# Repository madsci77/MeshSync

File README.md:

# MeshSync
A simple mobile ad hoc network designed to synchronize EL wire or LEDs on Burning Man costumes

I created this project back in 2012 with the goal of building a low cost device (around USD $10) that would plug in between a user's EL wire inverter and the EL wire on their costume or bike and automatically synchronize flashing patterns with other users around them.

It worked pretty well, but it turned out to be nearly impossible to get enough people together at the same time to do any of the more elaborate patterns.  Around 40 units were built.

Also included is a visual simulator written in VB to test out various aspects of the protocol.  It supports automatic partitioning and merging; if a group splits or multiple groups come together, they will automatically reorganize.  Patterns are chosen that are appropriate for the number of group members.

It's a mesh network and in the pathological case of nodes strung out so that each can only hear one node to either side, it'll still converge within a few network cycles.

Very little data is carried over the network; it's just timing information, group membership, and the currently running pattern.

The lowest hardware ID chooses the pattern.  Hardware ID 0 is reserved for a manual control device with a selector button.  Absent a manual control, patterns are chosen randomly.

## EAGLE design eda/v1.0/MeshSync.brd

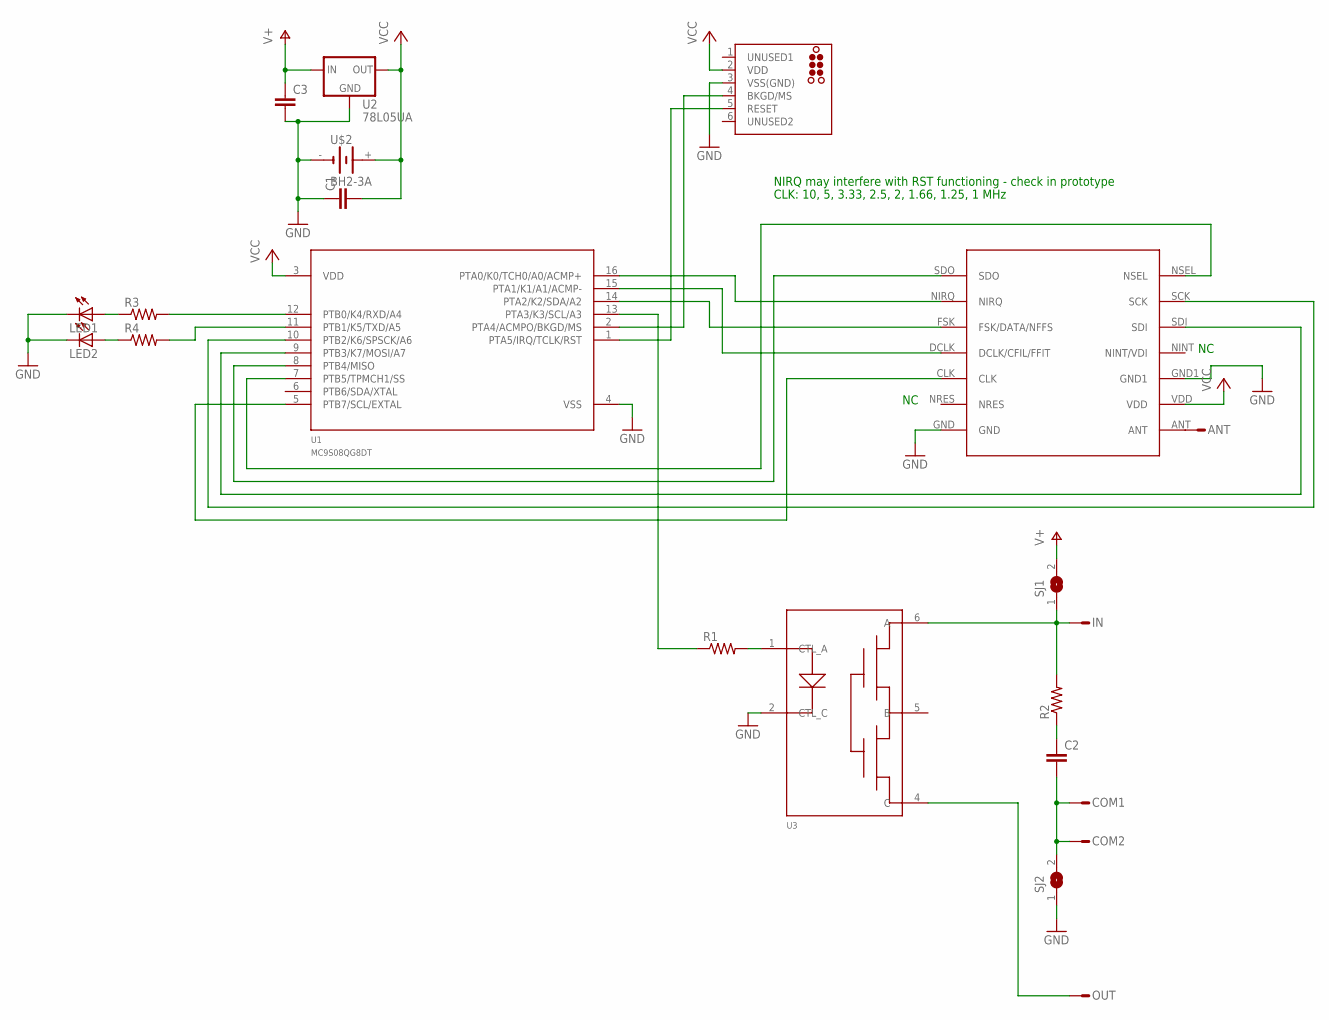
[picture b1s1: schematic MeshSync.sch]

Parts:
ANT: PIN; PINHEAD-1
C1: C-EUC0805K; C0805K
C2, C3: C-EUC0603K; C0603K
COM1, COM2: PIN; PINHEAD-1
IN: PIN; PINHEAD-1
LED1, LED2: LEDCHIPLED_0603; CHIPLED_0603
OUT: PIN; PINHEAD-1
R1, R2, R3, R4: R0603
SJ1, SJ2: SJW
U1: MC9S08QG8DT; TSSOP16
U2: 78L05UA; SOT89
U3: PVT312; DIL06-SMT
U$1: TC2030-MCP-NL
U$2: BH2-3A
XCVR: RFM12B

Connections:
GND: C1.1, C3.2, LED1.C, LED2.C, SJ2.1, U1.4 (VSS), U2.2 (GND), U3.2 (CTL_C), U$1.3 (VSS(GND)), U$2.-, XCVR.GND, XCVR.GND1
unnamed: U1.2 (PTA4/ACMPO/BKGD/MS), U$1.4 (BKGD/MS)
unnamed: U1.1 (PTA5/IRQ/TCLK/RST), U$1.5 (RESET)
unnamed: R1.2, U3.1 (CTL_A)
unnamed: U1.8 (PTB4/MISO), XCVR.SDO
unnamed: U1.9 (PTB3/K7/MOSI/A7), XCVR.SDI
unnamed: U1.10 (PTB2/K6/SPSCK/A6), XCVR.SCK
unnamed: U1.7 (PTB5/TPMCH1/SS), XCVR.NSEL
unnamed: U1.16 (PTA0/K0/TCH0/A0/ACMP+), XCVR.NIRQ
unnamed: U1.5 (PTB7/SCL/EXTAL), XCVR.CLK
unnamed: U1.15 (PTA1/K1/A1/ACMP-), XCVR.DCLK (DCLK/CFIL/FFIT)
unnamed: U1.14 (PTA2/K2/SDA/A2), XCVR.FSK (FSK/DATA/NFFS)
unnamed: ANT.1, XCVR.ANT
unnamed: R1.1, U1.13 (PTA3/K3/SCL/A3)
unnamed: IN.1, R2.2, SJ1.1, U3.6 (A)
unnamed: OUT.1, U3.4 (C)
unnamed: C2.1, R2.1
unnamed: C2.2, COM1.1, COM2.1, SJ2.2
unnamed: R4.2, U1.11 (PTB1/K5/TXD/A5)
unnamed: R3.2, U1.12 (PTB0/K4/RXD/A4)
unnamed: LED1.A, R3.1
unnamed: LED2.A, R4.1
V+: C3.1, SJ1.2, U2.3 (IN)
VCC: C1.2, U1.3 (VDD), U2.1 (OUT), U$1.2 (VDD), U$2.+, XCVR.VDD

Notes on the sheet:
CLK: 10, 5, 3.33, 2.5, 2, 1.66, 1.25, 1 MHz
NIRQ may interfere with RST functioning - check in prototype

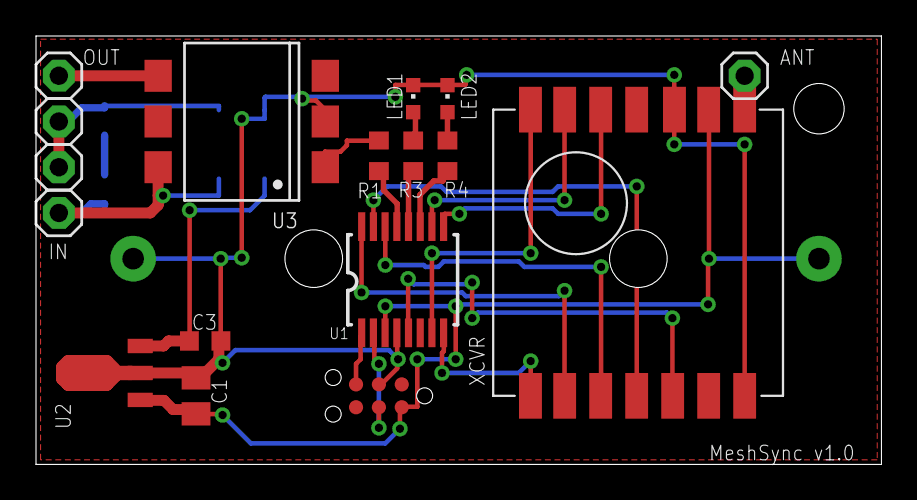
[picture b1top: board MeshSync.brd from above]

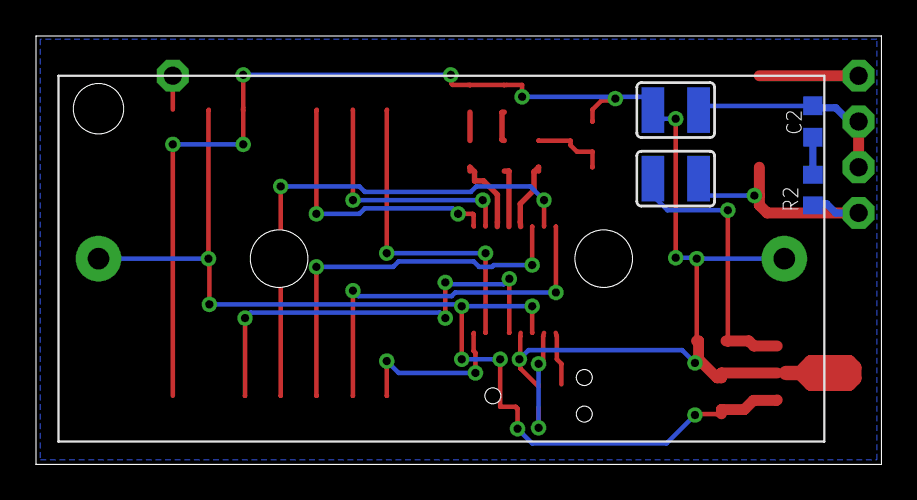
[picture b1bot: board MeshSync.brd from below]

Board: 2 copper layers, 47.0 x 23.8 mm, 22 parts (5 on the bottom side), 24 nets.

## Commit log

2017-05-16 Created repository

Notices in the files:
parts and their libraries:
scott: ©2009 ROFA.cz
